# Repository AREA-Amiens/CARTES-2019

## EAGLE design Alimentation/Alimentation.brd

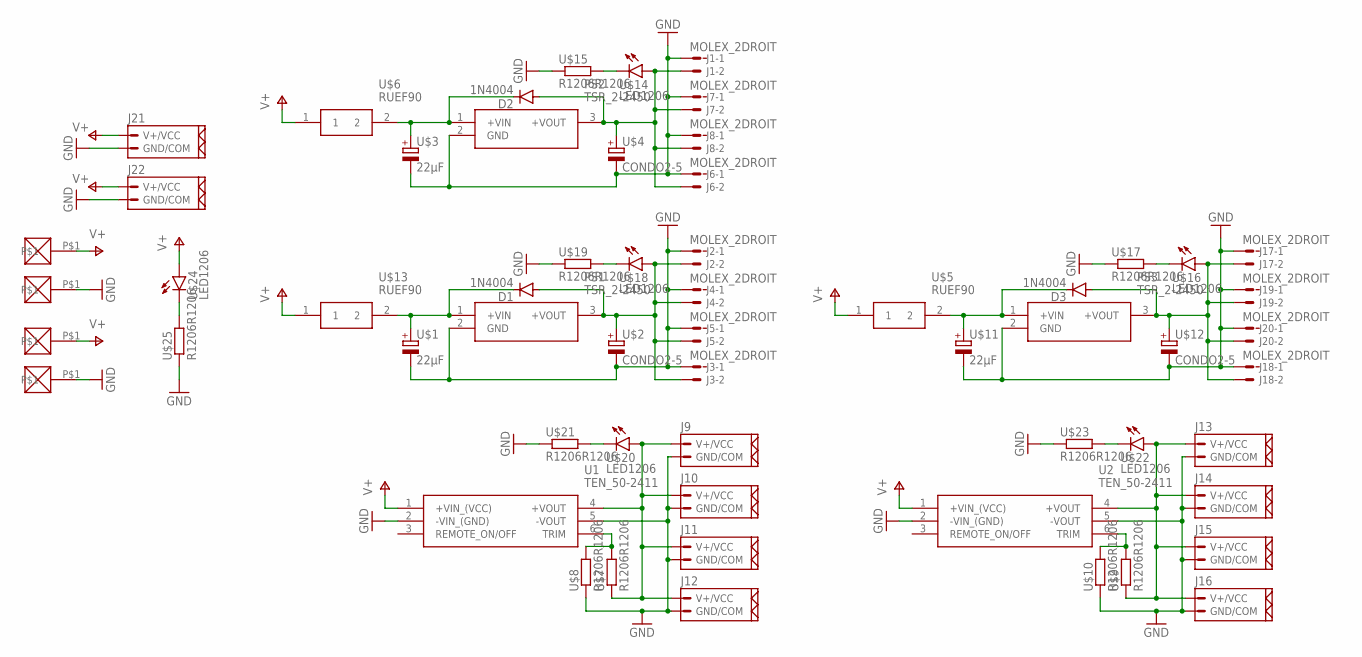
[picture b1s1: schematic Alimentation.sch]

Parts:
D1, D2, D3: 1N4004; DO41-10
J1, J2, J3, J4, J5, J6, J7, J8, J17, J18, J19, J20: MOLEX_2DROIT; CON_2_DROIT
J9, J10, J13, J14: MOLEX_2_PUISSDROIT; CON_2_PUISS_DROIT
J11, J12, J15, J16, J21, J22: MOLEX_2_PUISS90°; CON_2_PUISS_90°
PS1, PS2, PS3: TSR_2-2450; TSR-2
U1, U2: TEN_50-2411
U$1, U$3, U$11: 22µF; E2-5
U$2, U$4, U$12: CONDO2-5; E2-5
U$5, U$6, U$13: RUEF90; RUEF090
U$7, U$8, U$9, U$10, U$15, U$17, U$19, U$21, U$23, U$25: R1206R1206; R1206
U$14, U$16, U$18, U$20, U$22, U$24: LED1206; 1206
U$26, U$27, U$28, U$29: BAT_WIRE_SOLD; LARGE_PAD_BATT

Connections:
GND: J1.1, J2.1, J3.1, J4.1, J5.1, J6.1, J7.1, J8.1, J9.1 (GND/COM), J10.1 (GND/COM), J11.P$1 (GND/COM), J12.P$1 (GND/COM), J13.1 (GND/COM), J14.1 (GND/COM), J15.P$1 (GND/COM), J16.P$1 (GND/COM), J17.1, J18.1, J19.1, J20.1, J21.P$1 (GND/COM), J22.P$1 (GND/COM), PS1.2 (GND), PS2.2 (GND), PS3.2 (GND), U1.2 (-VIN_(GND)), U1.5 (-VOUT), U2.2 (-VIN_(GND)), U2.5 (-VOUT), U$1.-, U$2.-, U$3.-, U$4.-, U$8.1, U$10.1, U$11.-, U$12.-, U$15.1, U$17.1, U$19.1, U$21.1, U$23.1, U$25.1, U$26.P$1, U$28.P$1
unnamed: D1.C, PS1.1 (+VIN), U$1.+, U$13.2
unnamed: D2.C, PS2.1 (+VIN), U$3.+, U$6.2
unnamed: D2.A, J1.2, J6.2, J7.2, J8.2, PS2.3 (+VOUT), U$4.+, U$14.A
unnamed: J9.2 (V+/VCC), J10.2 (V+/VCC), J11.P$2 (V+/VCC), J12.P$2 (V+/VCC), U1.4 (+VOUT), U$7.1, U$20.A
unnamed: U1.6 (TRIM), U$7.2, U$8.2
unnamed: D1.A, J2.2, J3.2, J4.2, J5.2, PS1.3 (+VOUT), U$2.+, U$18.A
unnamed: J13.2 (V+/VCC), J14.2 (V+/VCC), J15.P$2 (V+/VCC), J16.P$2 (V+/VCC), U2.4 (+VOUT), U$9.1, U$22.A
unnamed: U2.6 (TRIM), U$9.2, U$10.2
unnamed: D3.C, PS3.1 (+VIN), U$5.2, U$11.+
unnamed: D3.A, J17.2, J18.2, J19.2, J20.2, PS3.3 (+VOUT), U$12.+, U$16.A
unnamed: U$14.C, U$15.2
unnamed: U$16.C, U$17.2
unnamed: U$18.C, U$19.2
unnamed: U$20.C, U$21.2
unnamed: U$22.C, U$23.2
unnamed: U$24.C, U$25.2
V+: J21.P$2 (V+/VCC), J22.P$2 (V+/VCC), U1.1 (+VIN_(VCC)), U2.1 (+VIN_(VCC)), U$5.1, U$6.1, U$13.1, U$24.A, U$27.P$1, U$29.P$1

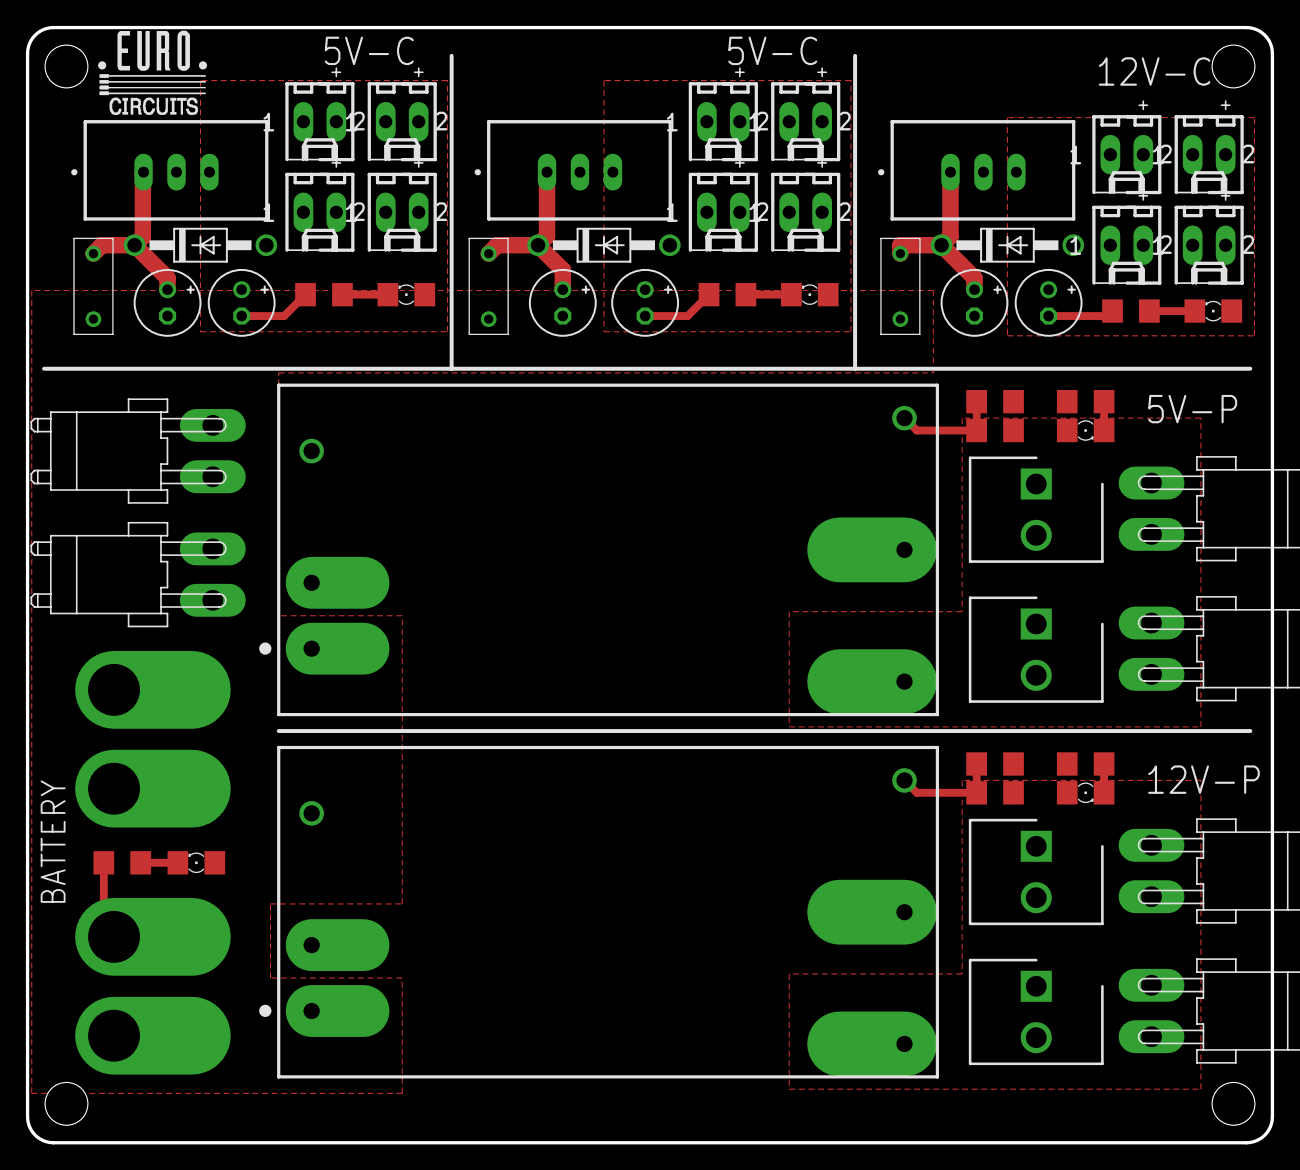
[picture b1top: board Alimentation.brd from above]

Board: 2 copper layers, 96.0 x 86.0 mm, 59 parts (0 on the bottom side), 18 nets.

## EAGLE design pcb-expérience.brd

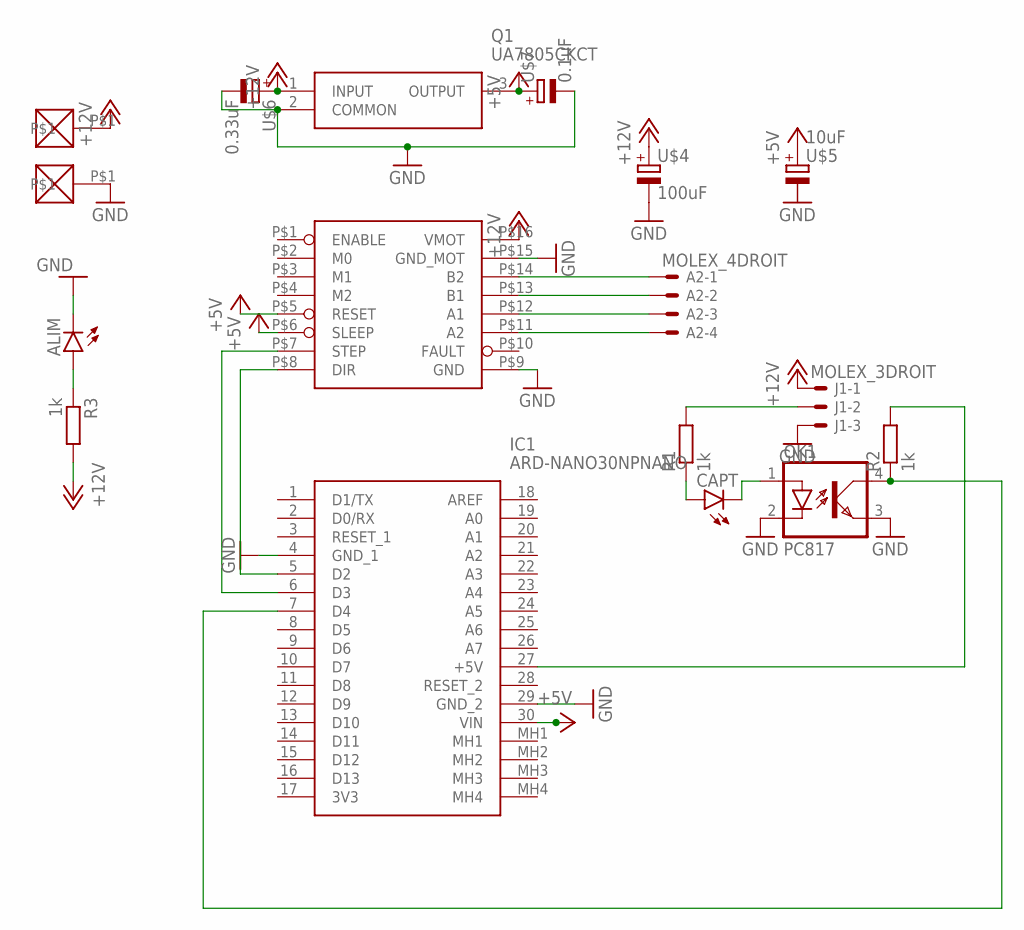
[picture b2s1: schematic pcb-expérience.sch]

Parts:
A2: MOLEX_4DROIT; CON_4_DROIT
ALIM: LED5MM
CAPT: LED5MM
IC1: ARD-NANO30NPNANO; ARDNANO30NP
J1: MOLEX_3DROIT; CON_3_DROIT
OK1: PC817; DIL04
Q1: UA7805CKCT; TO254P465X1016X1883-3P
R1, R3: 1k; 0207/2V
R2: 1k; 0207/7
U$1: DRV8825
U$2, U$3: BAT_WIRE_SOLD; LARGE_PAD_BATT
U$4: 100uF; E3,5-8
U$5: 10uF; E2-5
U$6: 0.33uF; E2-5
U$7: 0.1uF; E2-5

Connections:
+5V: IC1.30 (VIN), Q1.3 (OUTPUT), U$1.P$5 (RESET), U$1.P$6 (SLEEP), U$5.+, U$7.+
+12V: J1.1, Q1.1 (INPUT), R3.2, U$1.P$16 (VMOT), U$2.P$1, U$4.+, U$6.+
GND: ALIM.K (C), IC1.4 (GND_1), IC1.29 (GND_2), J1.3, OK1.2 (C), OK1.3 (EMIT), Q1.2 (COMMON), U$1.P$9 (GND), U$1.P$15 (GND_MOT), U$3.P$1, U$4.-, U$6.-, U$7.-
unnamed: J1.2, R1.2
unnamed: IC1.7 (D4), OK1.4 (COL), R2.1
unnamed: IC1.27 (+5V), R2.2
unnamed: A2.4, U$1.P$11 (A2)
unnamed: A2.3, U$1.P$12 (A1)
unnamed: A2.2, U$1.P$13 (B1)
unnamed: A2.1, U$1.P$14 (B2)
unnamed: ALIM.A, R3.1
unnamed: CAPT.K (C), OK1.1 (A)
unnamed: CAPT.A, R1.1
unnamed: IC1.5 (D2), U$1.P$8 (DIR)
unnamed: IC1.6 (D3), U$1.P$7 (STEP)

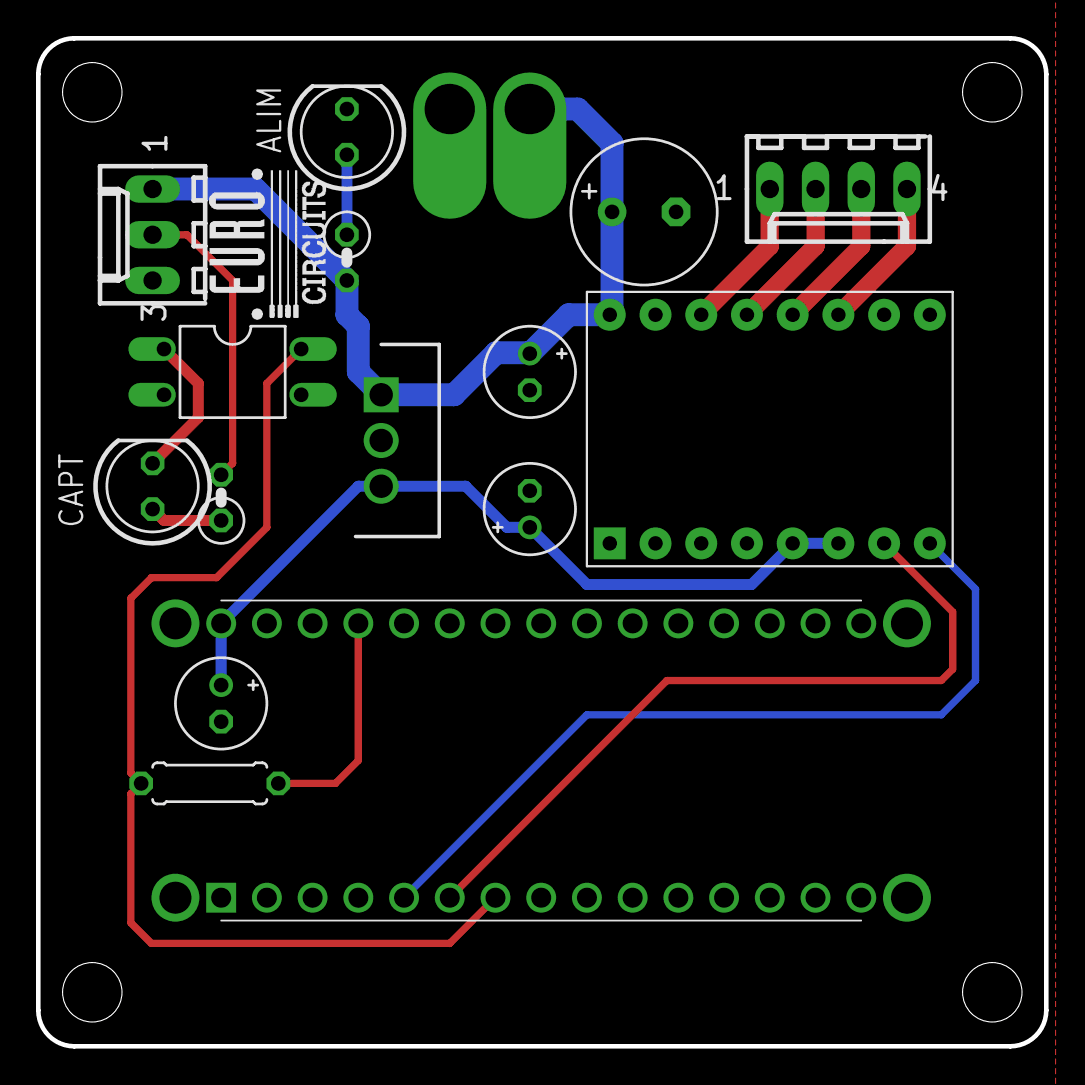
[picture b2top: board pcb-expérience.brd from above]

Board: 2 copper layers, 56.0 x 56.0 mm, 17 parts (0 on the bottom side), 15 nets.

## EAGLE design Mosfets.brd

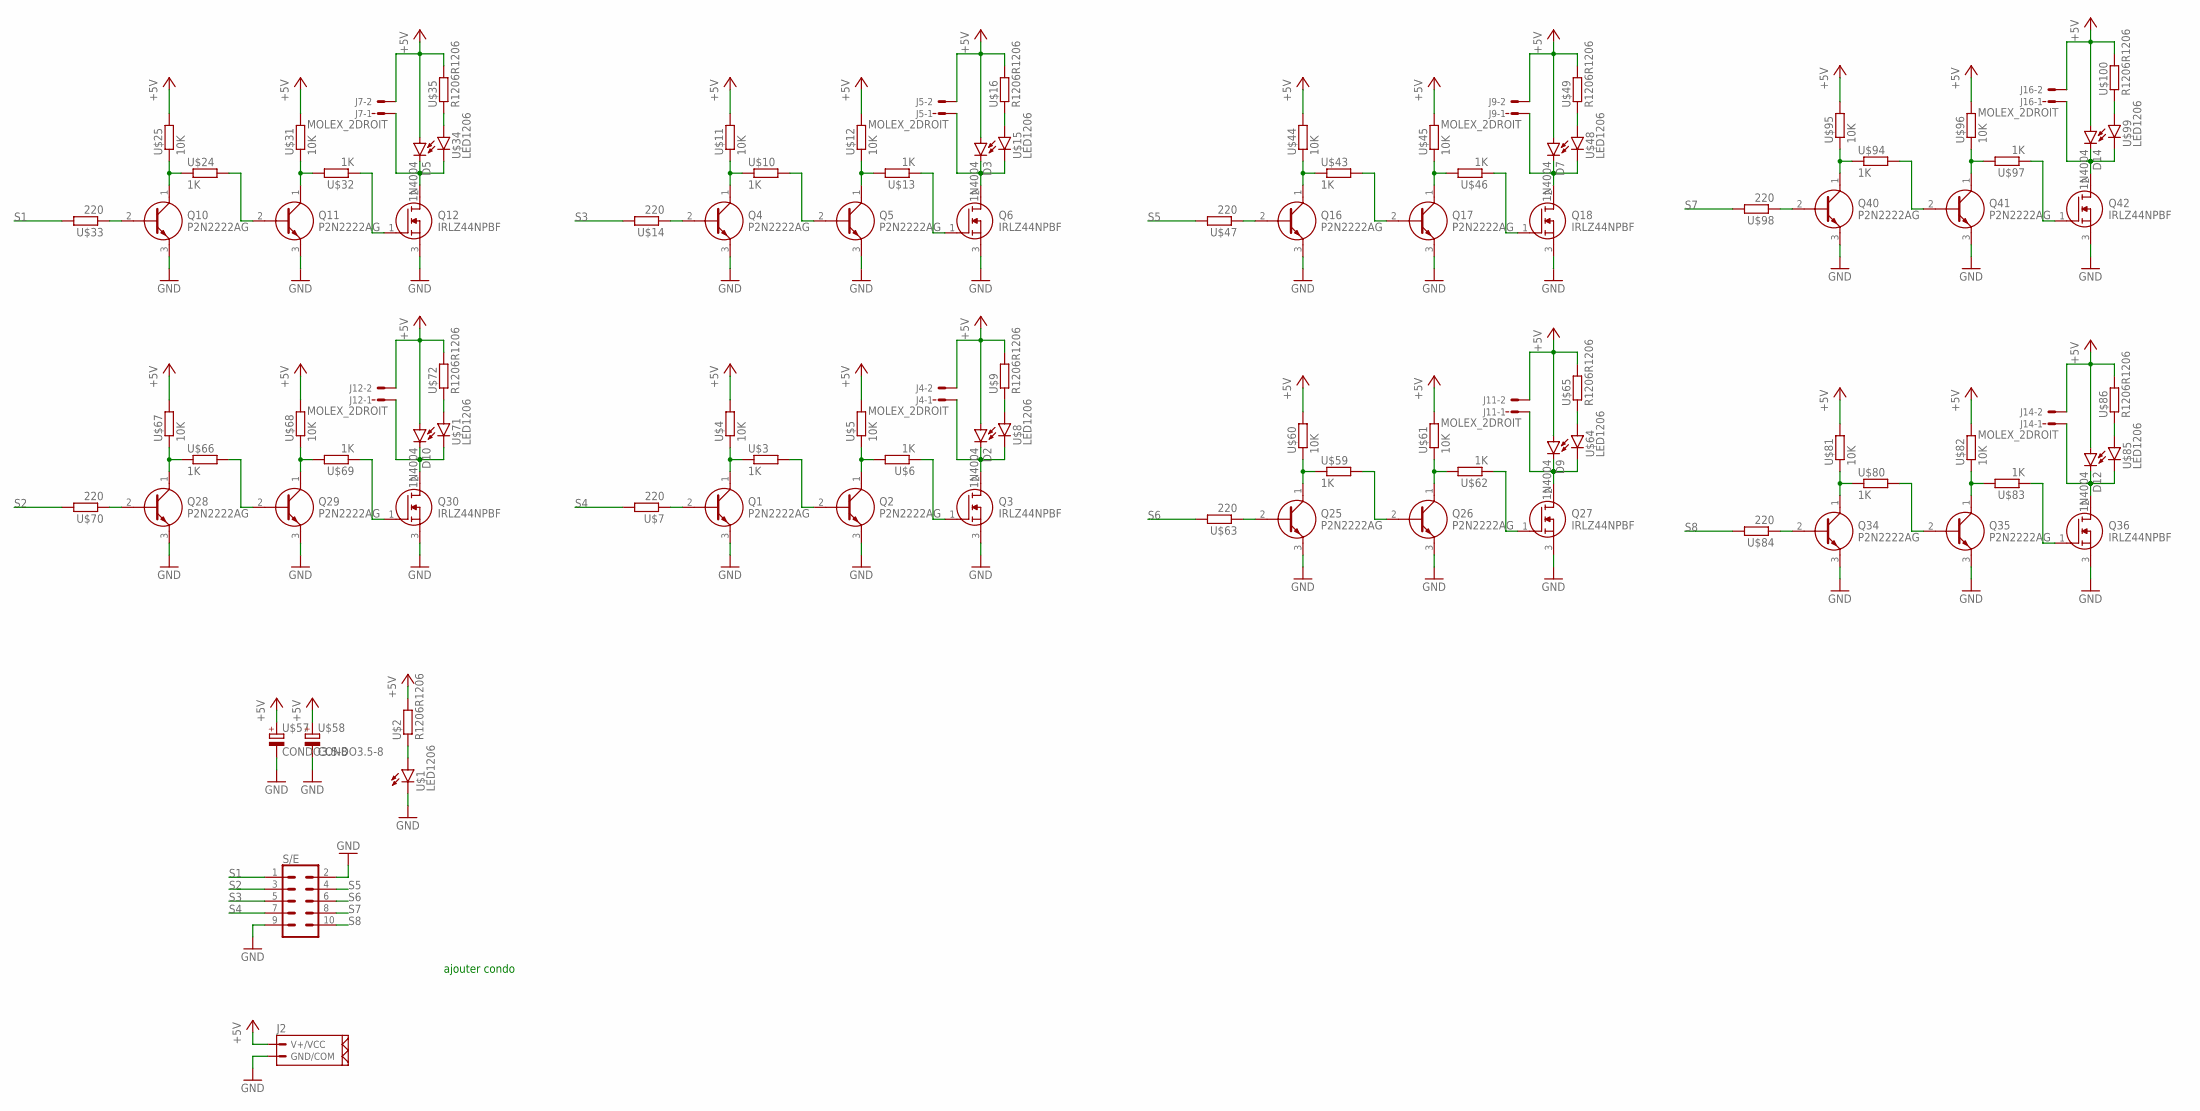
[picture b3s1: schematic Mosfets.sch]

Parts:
D2, D3, D5, D7, D9, D10, D12, D14: 1N4004; DO41-10
J2: MOLEX_2_PUISS90°; CON_2_PUISS_90°
J4, J5, J7, J9, J11, J12, J14, J16: MOLEX_2DROIT; CON_2_DROIT
Q1, Q2, Q4, Q5, Q10, Q11, Q16, Q17, Q25, Q26, Q28, Q29, Q34, Q35, Q40, Q41: P2N2222AG; TO-92
Q3, Q6, Q12, Q18, Q27, Q30, Q36, Q42: IRLZ44NPBF; TO254P469X1042X1967-3P
S/E: CON_5X2SHD; 2X5-SHROUDED
U$1, U$8, U$15, U$34, U$48, U$64, U$71, U$85, U$99: LED1206; 1206
U$2, U$9, U$16, U$35, U$49, U$65, U$72, U$86, U$100: R1206R1206; R1206
U$3, U$6, U$10, U$13, U$24, U$32, U$43, U$46, U$59, U$62, U$66, U$69, U$80, U$83, U$94, U$97: 1K; R1206
U$4, U$5, U$11, U$12, U$25, U$31, U$44, U$45, U$60, U$61, U$67, U$68, U$81, U$82, U$95, U$96: 10K; R1206
U$7, U$14, U$33, U$47, U$63, U$70, U$84, U$98: 220; R1206
U$57, U$58: CONDO3.5-8; E3,5-8

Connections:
+5V: D2.A, D3.A, D5.A, D7.A, D9.A, D10.A, D12.A, D14.A, J2.P$2 (V+/VCC), J4.2, J5.2, J7.2, J9.2, J11.2, J12.2, J14.2, J16.2, U$2.2, U$4.2, U$5.2, U$9.2, U$11.2, U$12.2, U$16.2, U$25.2, U$31.2, U$35.2, U$44.2, U$45.2, U$49.2, U$57.+, U$58.+, U$60.2, U$61.2, U$65.2, U$67.2, U$68.2, U$72.2, U$81.2, U$82.2, U$86.2, U$95.2, U$96.2, U$100.2
GND: J2.P$1 (GND/COM), Q1.3 (E), Q2.3 (E), Q3.3 (S), Q4.3 (E), Q5.3 (E), Q6.3 (S), Q10.3 (E), Q11.3 (E), Q12.3 (S), Q16.3 (E), Q17.3 (E), Q18.3 (S), Q25.3 (E), Q26.3 (E), Q27.3 (S), Q28.3 (E), Q29.3 (E), Q30.3 (S), Q34.3 (E), Q35.3 (E), Q36.3 (S), Q40.3 (E), Q41.3 (E), Q42.3 (S), S/E.2, S/E.9, U$1.C, U$57.-, U$58.-
unnamed: Q1.1 (C), U$3.1, U$4.1
unnamed: Q2.1 (C), U$5.1, U$6.2
unnamed: Q1.2 (B), U$7.1
unnamed: Q2.2 (B), U$3.2
unnamed: Q3.1 (G), U$6.1
unnamed: D2.C, J4.1, Q3.2 (D), U$8.C
unnamed: U$8.A, U$9.1
unnamed: Q4.1 (C), U$10.1, U$11.1
unnamed: Q5.1 (C), U$12.1, U$13.2
unnamed: Q4.2 (B), U$14.1
unnamed: Q5.2 (B), U$10.2
unnamed: Q6.1 (G), U$13.1
unnamed: D3.C, J5.1, Q6.2 (D), U$15.C
unnamed: Q28.1 (C), U$66.1, U$67.1
unnamed: U$15.A, U$16.1
unnamed: U$1.A, U$2.1
unnamed: Q10.1 (C), U$24.1, U$25.1
unnamed: Q11.1 (C), U$31.1, U$32.2
unnamed: Q10.2 (B), U$33.1
unnamed: Q11.2 (B), U$24.2
unnamed: Q12.1 (G), U$32.1
unnamed: D5.C, J7.1, Q12.2 (D), U$34.C
unnamed: U$34.A, U$35.1
unnamed: Q16.1 (C), U$43.1, U$44.1
unnamed: Q17.1 (C), U$45.1, U$46.2
unnamed: Q16.2 (B), U$47.1
unnamed: Q17.2 (B), U$43.2
unnamed: Q18.1 (G), U$46.1
unnamed: D7.C, J9.1, Q18.2 (D), U$48.C
unnamed: U$48.A, U$49.1
unnamed: Q29.1 (C), U$68.1, U$69.2
unnamed: Q25.1 (C), U$59.1, U$60.1
unnamed: Q26.1 (C), U$61.1, U$62.2
unnamed: Q25.2 (B), U$63.1
unnamed: Q26.2 (B), U$59.2
unnamed: Q27.1 (G), U$62.1
unnamed: D9.C, J11.1, Q27.2 (D), U$64.C
unnamed: U$64.A, U$65.1
unnamed: Q28.2 (B), U$70.1
unnamed: Q29.2 (B), U$66.2
unnamed: Q30.1 (G), U$69.1
unnamed: D10.C, J12.1, Q30.2 (D), U$71.C
unnamed: U$71.A, U$72.1
unnamed: Q34.1 (C), U$80.1, U$81.1
unnamed: Q35.1 (C), U$82.1, U$83.2
unnamed: Q34.2 (B), U$84.1
unnamed: Q35.2 (B), U$80.2
unnamed: Q36.1 (G), U$83.1
unnamed: D12.C, J14.1, Q36.2 (D), U$85.C
unnamed: U$85.A, U$86.1
unnamed: Q40.1 (C), U$94.1, U$95.1
unnamed: Q41.1 (C), U$96.1, U$97.2
unnamed: Q40.2 (B), U$98.1
unnamed: Q41.2 (B), U$94.2
unnamed: Q42.1 (G), U$97.1
unnamed: D14.C, J16.1, Q42.2 (D), U$99.C
unnamed: U$99.A, U$100.1
S1: S/E.1, U$33.2
S2: S/E.3, U$70.2
S3: S/E.5, U$14.2
S4: S/E.7, U$7.2
S5: S/E.4, U$47.2
S6: S/E.6, U$63.2
S7: S/E.8, U$98.2
S8: S/E.10, U$84.2

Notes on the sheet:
ajouter condo

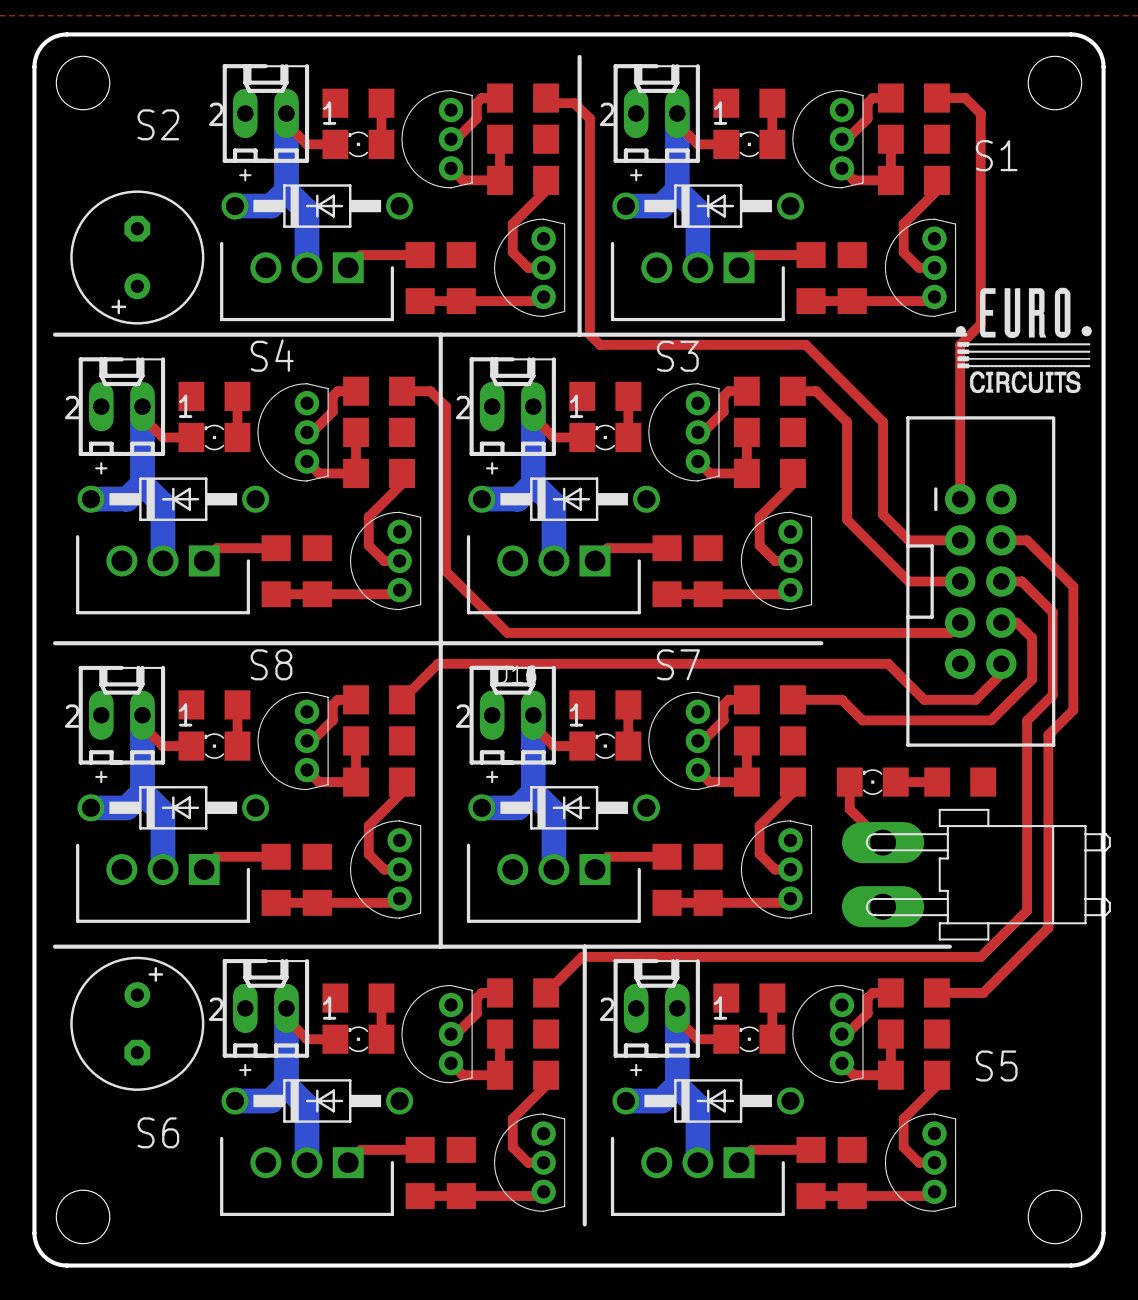
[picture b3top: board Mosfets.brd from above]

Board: 2 copper layers, 66.0 x 76.0 mm, 102 parts (0 on the bottom side), 67 nets.

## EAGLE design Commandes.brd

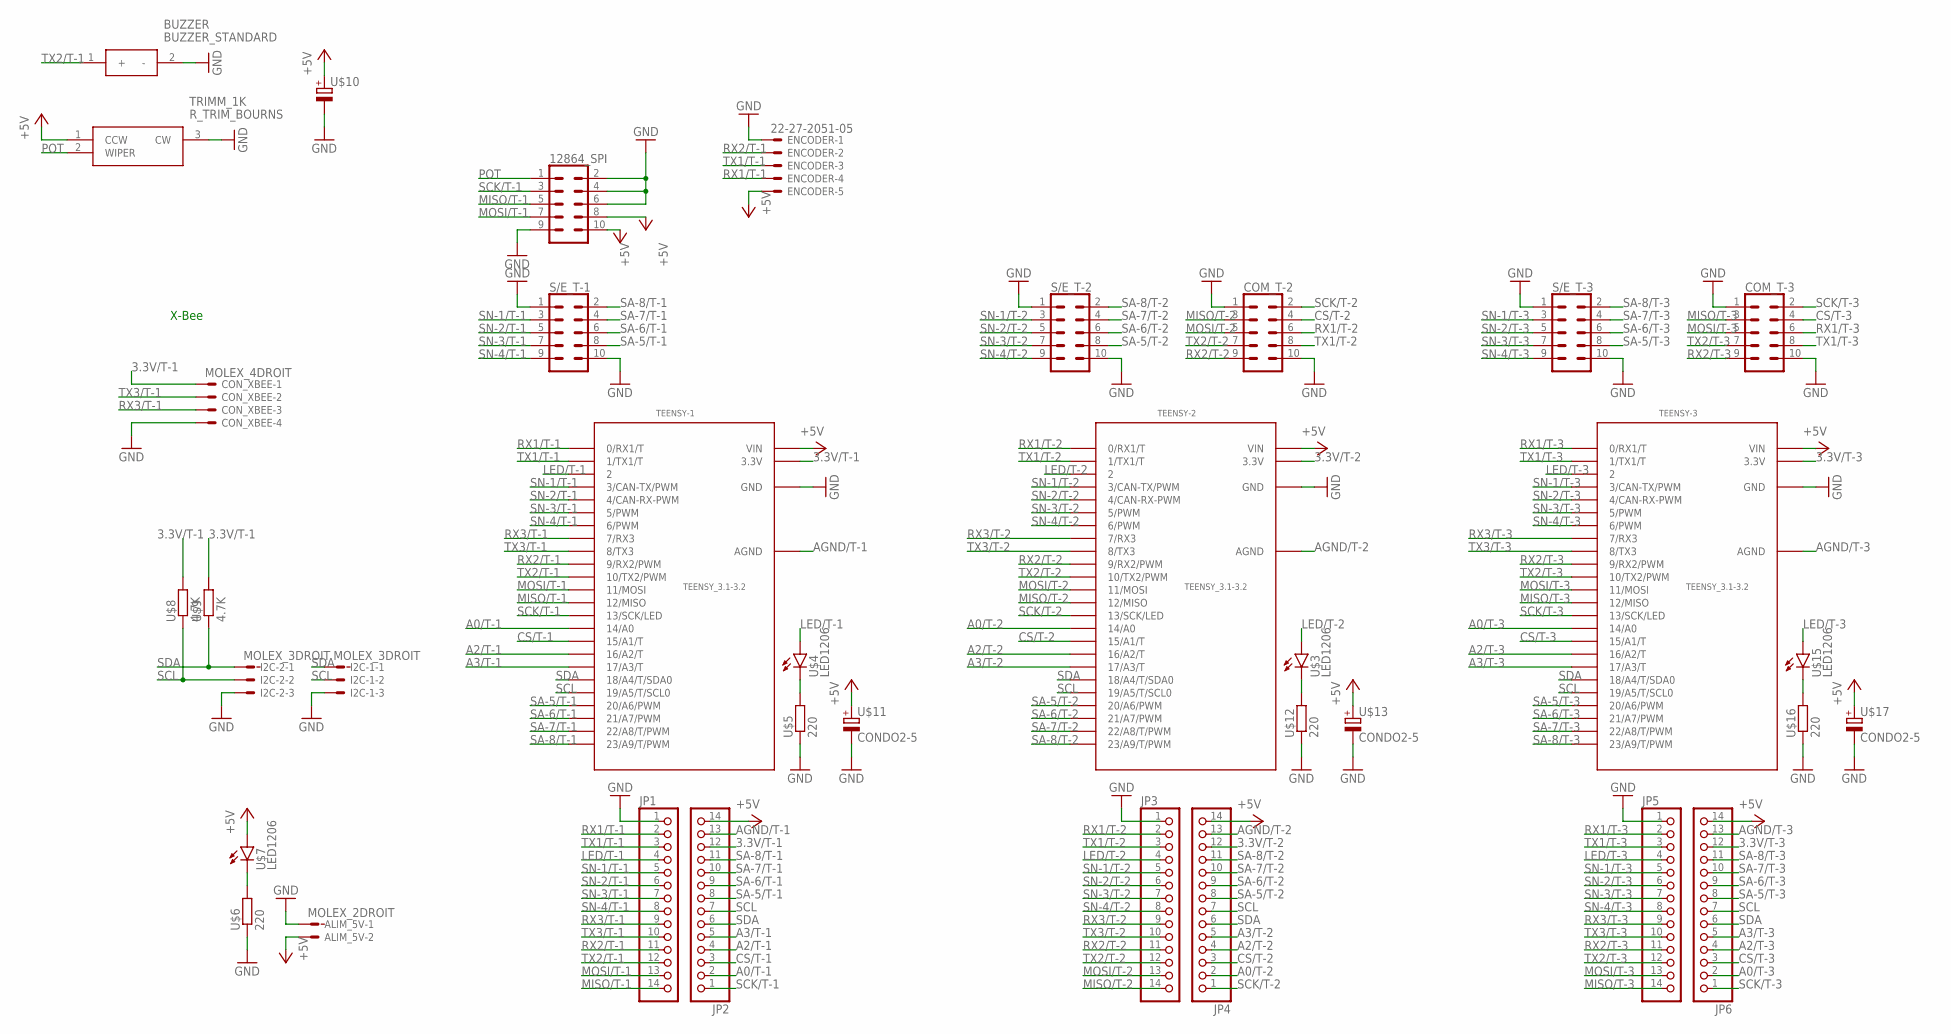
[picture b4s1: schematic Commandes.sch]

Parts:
12864_SPI: CON_5X2SHD; 2X5-SHROUDED
ALIM_5V: MOLEX_2DROIT; CON_2_DROIT
BUZZER: BUZZER_STANDARD; CEM-1203(42)
COM_T-2, COM_T-3: CON_5X2SHD; 2X5-SHROUDED
CON_XBEE: MOLEX_4DROIT; CON_4_DROIT
ENCODER: 22-27-2051-05; 6410-05
I2C-1, I2C-2: MOLEX_3DROIT; CON_3_DROIT
JP1, JP2, JP3, JP4, JP5, JP6: PINHD-1X14_2.54; 1X14
S/E_T-1, S/E_T-2, S/E_T-3: CON_5X2SHD; 2X5-SHROUDED
TEENSY-1, TEENSY-2, TEENSY-3: TEENSY_3.1-3.2; TEENSY_3.0-3.2&LC_OUTER_ROW
TRIMM_1K: R_TRIM_BOURNS; 3362P_1
U$3, U$4, U$7, U$15: LED1206; 1206
U$5, U$6, U$12, U$16: 220; R1206
U$8, U$9: 4.7K; R1206
U$10, U$11, U$13, U$17: CONDO2-5; E2-5

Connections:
3.3V/T-1: CON_XBEE.1, JP2.12, TEENSY-1.3.3V, U$8.2, U$9.2
3.3V/T-2: JP4.12, TEENSY-2.3.3V
3.3V/T-3: JP6.12, TEENSY-3.3.3V
+5V: 12864_SPI.8, 12864_SPI.10, ALIM_5V.2, ENCODER.5, JP2.14, JP4.14, JP6.14, TEENSY-1.V_IN (VIN), TEENSY-2.V_IN (VIN), TEENSY-3.V_IN (VIN), TRIMM_1K.1 (CCW), U$7.A, U$10.+, U$11.+, U$13.+, U$17.+
A0/T-1: JP2.2, TEENSY-1.14/A0
A0/T-2: JP4.2, TEENSY-2.14/A0
A0/T-3: JP6.2, TEENSY-3.14/A0
A2/T-1: JP2.4, TEENSY-1.16/A2 (16/A2/T)
A2/T-2: JP4.4, TEENSY-2.16/A2 (16/A2/T)
A2/T-3: JP6.4, TEENSY-3.16/A2 (16/A2/T)
A3/T-1: JP2.5, TEENSY-1.17/A3 (17/A3/T)
A3/T-2: JP4.5, TEENSY-2.17/A3 (17/A3/T)
A3/T-3: JP6.5, TEENSY-3.17/A3 (17/A3/T)
AGND/T-1: JP2.13, TEENSY-1.AGND
AGND/T-2: JP4.13, TEENSY-2.AGND
AGND/T-3: JP6.13, TEENSY-3.AGND
CS/T-1: JP2.3, TEENSY-1.15/A1 (15/A1/T)
CS/T-2: COM_T-2.4, JP4.3, TEENSY-2.15/A1 (15/A1/T)
CS/T-3: COM_T-3.4, JP6.3, TEENSY-3.15/A1 (15/A1/T)
GND: 12864_SPI.2, 12864_SPI.4, 12864_SPI.6, 12864_SPI.9, ALIM_5V.1, BUZZER.2 (-), COM_T-2.1, COM_T-2.10, COM_T-3.1, COM_T-3.10, CON_XBEE.4, ENCODER.1, I2C-1.3, I2C-2.3, JP1.1, JP3.1, JP5.1, S/E_T-1.1, S/E_T-1.10, S/E_T-2.1, S/E_T-2.10, S/E_T-3.1, S/E_T-3.10, TEENSY-1.GND, TEENSY-2.GND, TEENSY-3.GND, TRIMM_1K.3 (CW), U$5.1, U$6.1, U$10.-, U$11.-, U$12.1, U$13.-, U$16.1, U$17.-
LED/T-1: JP1.4, TEENSY-1.2, U$4.A
LED/T-2: JP3.4, TEENSY-2.2, U$3.A
LED/T-3: JP5.4, TEENSY-3.2, U$15.A
MISO/T-1: 12864_SPI.5, JP1.14, TEENSY-1.12 (12/MISO)
MISO/T-2: COM_T-2.3, JP3.14, TEENSY-2.12 (12/MISO)
MISO/T-3: COM_T-3.3, JP5.14, TEENSY-3.12 (12/MISO)
MOSI/T-1: 12864_SPI.7, JP1.13, TEENSY-1.11 (11/MOSI)
MOSI/T-2: COM_T-2.5, JP3.13, TEENSY-2.11 (11/MOSI)
MOSI/T-3: COM_T-3.5, JP5.13, TEENSY-3.11 (11/MOSI)
unnamed: U$4.C, U$5.2
unnamed: U$3.C, U$12.2
unnamed: U$15.C, U$16.2
unnamed: U$6.2, U$7.C
POT: 12864_SPI.1, TRIMM_1K.2 (WIPER)
RX1/T-1: ENCODER.4, JP1.2, TEENSY-1.0 (0/RX1/T)
RX1/T-2: COM_T-2.6, JP3.2, TEENSY-2.0 (0/RX1/T)
RX1/T-3: COM_T-3.6, JP5.2, TEENSY-3.0 (0/RX1/T)
RX2/T-1: ENCODER.2, JP1.11, TEENSY-1.9 (9/RX2/PWM)
RX2/T-2: COM_T-2.9, JP3.11, TEENSY-2.9 (9/RX2/PWM)
RX2/T-3: COM_T-3.9, JP5.11, TEENSY-3.9 (9/RX2/PWM)
RX3/T-1: CON_XBEE.3, JP1.9, TEENSY-1.7 (7/RX3)
RX3/T-2: JP3.9, TEENSY-2.7 (7/RX3)
RX3/T-3: JP5.9, TEENSY-3.7 (7/RX3)
SA-5/T-1: JP2.8, S/E_T-1.8, TEENSY-1.20/A6 (20/A6/PWM)
SA-5/T-2: JP4.8, S/E_T-2.8, TEENSY-2.20/A6 (20/A6/PWM)
SA-5/T-3: JP6.8, S/E_T-3.8, TEENSY-3.20/A6 (20/A6/PWM)
SA-6/T-1: JP2.9, S/E_T-1.6, TEENSY-1.21/A7 (21/A7/PWM)
SA-6/T-2: JP4.9, S/E_T-2.6, TEENSY-2.21/A7 (21/A7/PWM)
SA-6/T-3: JP6.9, S/E_T-3.6, TEENSY-3.21/A7 (21/A7/PWM)
SA-7/T-1: JP2.10, S/E_T-1.4, TEENSY-1.22/A8 (22/A8/T/PWM)
SA-7/T-2: JP4.10, S/E_T-2.4, TEENSY-2.22/A8 (22/A8/T/PWM)
SA-7/T-3: JP6.10, S/E_T-3.4, TEENSY-3.22/A8 (22/A8/T/PWM)
SA-8/T-1: JP2.11, S/E_T-1.2, TEENSY-1.23/A9 (23/A9/T/PWM)
SA-8/T-2: JP4.11, S/E_T-2.2, TEENSY-2.23/A9 (23/A9/T/PWM)
SA-8/T-3: JP6.11, S/E_T-3.2, TEENSY-3.23/A9 (23/A9/T/PWM)
SCK/T-1: 12864_SPI.3, JP2.1, TEENSY-1.13 (13/SCK/LED)
SCK/T-2: COM_T-2.2, JP4.1, TEENSY-2.13 (13/SCK/LED)
SCK/T-3: COM_T-3.2, JP6.1, TEENSY-3.13 (13/SCK/LED)
SCL: I2C-1.2, I2C-2.2, JP2.7, JP4.7, JP6.7, TEENSY-1.19/A5 (19/A5/T/SCL0), TEENSY-2.19/A5 (19/A5/T/SCL0), TEENSY-3.19/A5 (19/A5/T/SCL0), U$8.1
SDA: I2C-1.1, I2C-2.1, JP2.6, JP4.6, JP6.6, TEENSY-1.18/A4 (18/A4/T/SDA0), TEENSY-2.18/A4 (18/A4/T/SDA0), TEENSY-3.18/A4 (18/A4/T/SDA0), U$9.1
SN-1/T-1: JP1.5, S/E_T-1.3, TEENSY-1.3 (3/CAN-TX/PWM)
SN-1/T-2: JP3.5, S/E_T-2.3, TEENSY-2.3 (3/CAN-TX/PWM)
SN-1/T-3: JP5.5, S/E_T-3.3, TEENSY-3.3 (3/CAN-TX/PWM)
SN-2/T-1: JP1.6, S/E_T-1.5, TEENSY-1.4 (4/CAN-RX-PWM)
SN-2/T-2: JP3.6, S/E_T-2.5, TEENSY-2.4 (4/CAN-RX-PWM)
SN-2/T-3: JP5.6, S/E_T-3.5, TEENSY-3.4 (4/CAN-RX-PWM)
SN-3/T-1: JP1.7, S/E_T-1.7, TEENSY-1.5 (5/PWM)
SN-3/T-2: JP3.7, S/E_T-2.7, TEENSY-2.5 (5/PWM)
SN-3/T-3: JP5.7, S/E_T-3.7, TEENSY-3.5 (5/PWM)
SN-4/T-1: JP1.8, S/E_T-1.9, TEENSY-1.6 (6/PWM)
SN-4/T-2: JP3.8, S/E_T-2.9, TEENSY-2.6 (6/PWM)
SN-4/T-3: JP5.8, S/E_T-3.9, TEENSY-3.6 (6/PWM)
TX1/T-1: ENCODER.3, JP1.3, TEENSY-1.1 (1/TX1/T)
TX1/T-2: COM_T-2.8, JP3.3, TEENSY-2.1 (1/TX1/T)
TX1/T-3: COM_T-3.8, JP5.3, TEENSY-3.1 (1/TX1/T)
TX2/T-1: BUZZER.1 (+), JP1.12, TEENSY-1.10 (10/TX2/PWM)
TX2/T-2: COM_T-2.7, JP3.12, TEENSY-2.10 (10/TX2/PWM)
TX2/T-3: COM_T-3.7, JP5.12, TEENSY-3.10 (10/TX2/PWM)
TX3/T-1: CON_XBEE.2, JP1.10, TEENSY-1.8 (8/TX3)
TX3/T-2: JP3.10, TEENSY-2.8 (8/TX3)
TX3/T-3: JP5.10, TEENSY-3.8 (8/TX3)

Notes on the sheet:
X-Bee

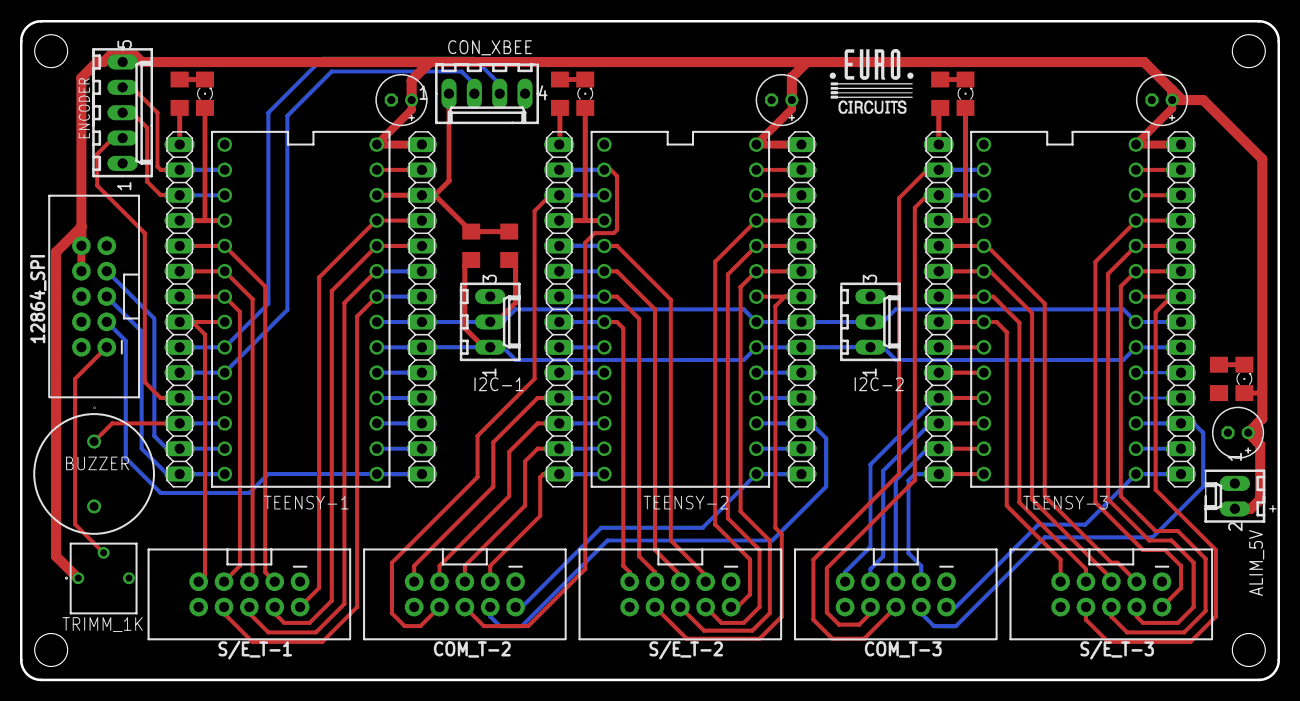
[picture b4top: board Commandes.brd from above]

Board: 2 copper layers, 126.0 x 66.0 mm, 36 parts (0 on the bottom side), 81 nets.

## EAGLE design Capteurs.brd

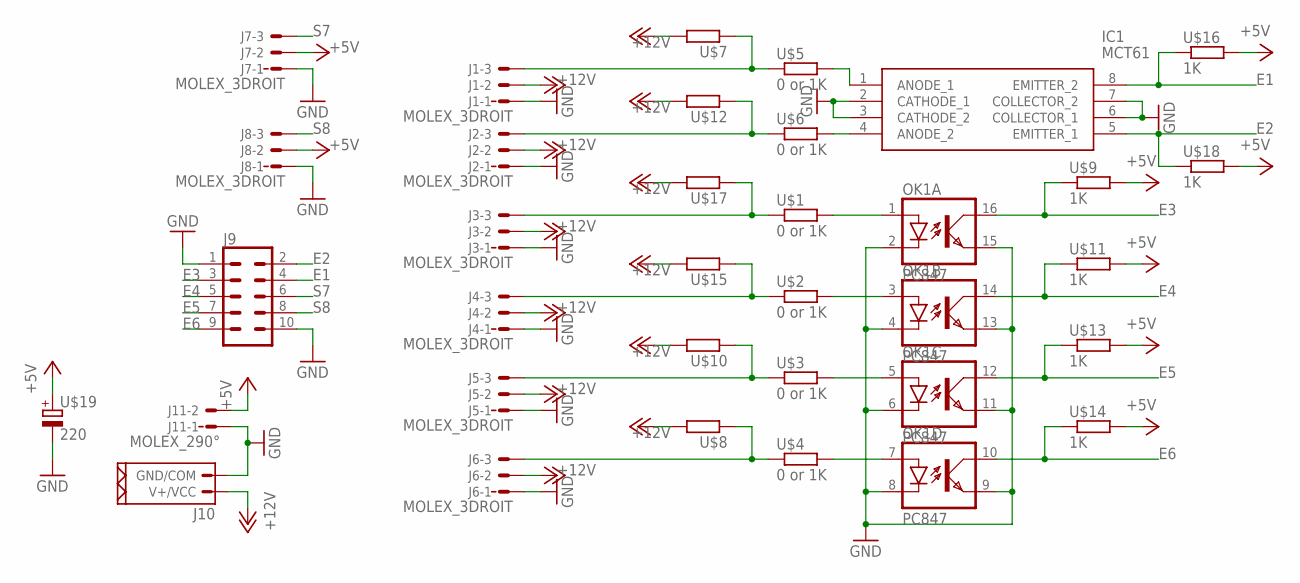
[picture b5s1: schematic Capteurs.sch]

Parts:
IC1: MCT61; DIP762W56P254L940H508Q8N
J1, J2, J3, J4, J5, J6, J7, J8: MOLEX_3DROIT; CON_3_DROIT
J9: CON_5X2SHD; 2X5-SHROUDED
J10: MOLEX_2_PUISS90°; CON_2_PUISS_90°
J11: MOLEX_290°; CON_2_90°
OK1: PC847; DIL16
U$1, U$2, U$3, U$4, U$5, U$6: 0 or 1K; R1206
U$7, U$8, U$10, U$12, U$15, U$17: NULL or 500; R1206
U$9, U$11, U$13, U$14, U$16, U$18: 1K; R1206
U$19: 220; E3,5-8

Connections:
+5V: J7.2, J8.2, J11.2, U$9.2, U$11.2, U$13.2, U$14.2, U$16.2, U$18.2, U$19.+
+12V: J1.2, J2.2, J3.2, J4.2, J5.2, J6.2, J10.P$2 (V+/VCC), U$7.2, U$8.2, U$10.2, U$12.2, U$15.2, U$17.2
E1: IC1.8 (EMITTER_2), J9.4, U$16.1
E2: IC1.5 (EMITTER_1), J9.2, U$18.1
E3: J9.3, OK1.16 (COL), U$9.1
E4: J9.5, OK1.14 (COL), U$11.1
E5: J9.7, OK1.12 (COL), U$13.1
E6: J9.9, OK1.10 (COL), U$14.1
GND: IC1.2 (CATHODE_1), IC1.3 (CATHODE_2), IC1.6 (COLLECTOR_1), IC1.7 (COLLECTOR_2), J1.1, J2.1, J3.1, J4.1, J5.1, J6.1, J7.1, J8.1, J9.1, J9.10, J10.P$1 (GND/COM), J11.1, OK1.2 (C), OK1.4 (C), OK1.6 (C), OK1.8 (C), OK1.9 (EMIT), OK1.11 (EMIT), OK1.13 (EMIT), OK1.15 (EMIT), U$19.-
unnamed: OK1.1 (A), U$1.2
unnamed: OK1.3 (A), U$2.2
unnamed: OK1.5 (A), U$3.2
unnamed: OK1.7 (A), U$4.2
unnamed: J3.3, U$1.1, U$17.1
unnamed: J4.3, U$2.1, U$15.1
unnamed: IC1.1 (ANODE_1), U$5.2
unnamed: IC1.4 (ANODE_2), U$6.2
unnamed: J5.3, U$3.1, U$10.1
unnamed: J6.3, U$4.1, U$8.1
unnamed: J2.3, U$6.1, U$12.1
unnamed: J1.3, U$5.1, U$7.1
S7: J7.3, J9.6
S8: J8.3, J9.8

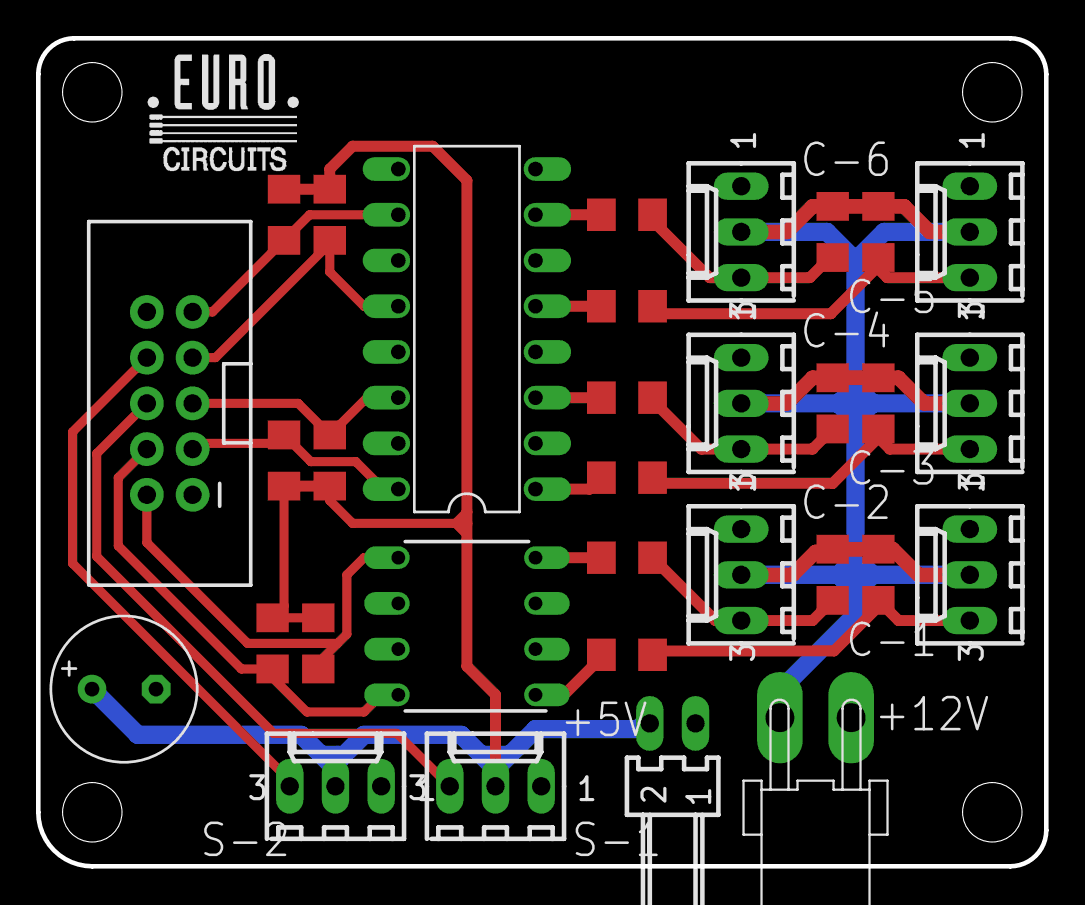
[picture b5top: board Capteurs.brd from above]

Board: 2 copper layers, 56.0 x 46.0 mm, 32 parts (0 on the bottom side), 23 nets.

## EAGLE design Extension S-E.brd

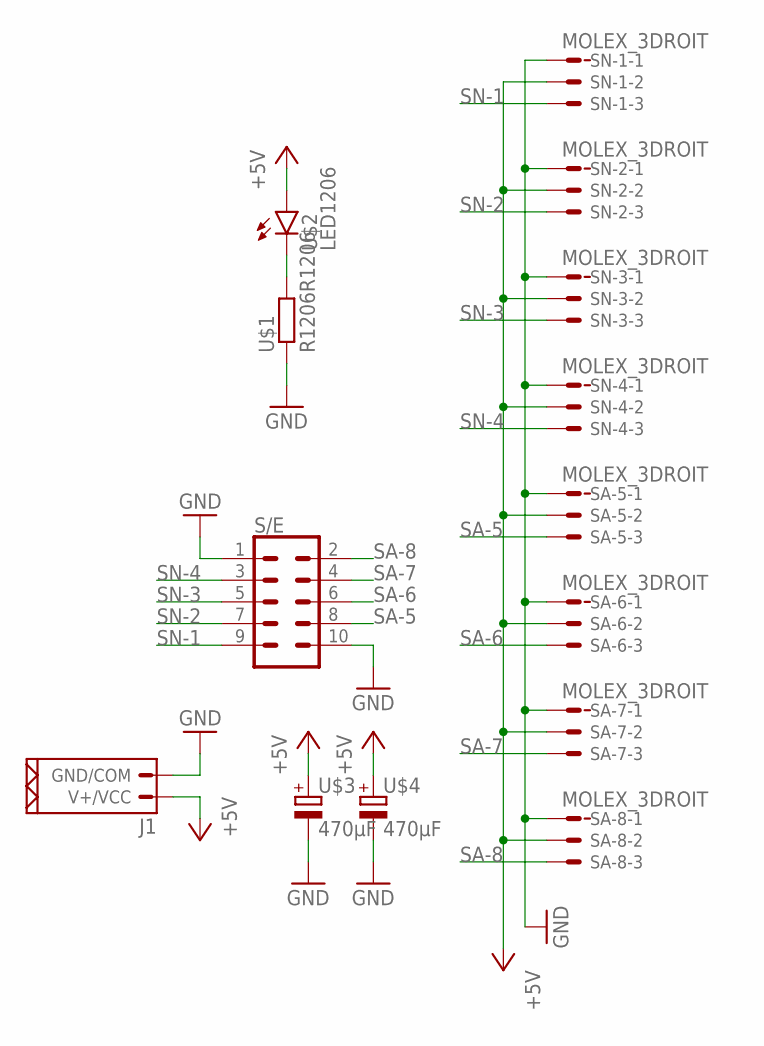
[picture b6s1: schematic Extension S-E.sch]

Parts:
J1: MOLEX_2_PUISS90°; CON_2_PUISS_90°
S/E: CON_5X2SHD; 2X5-SHROUDED
SA-5, SA-6, SA-7, SA-8: MOLEX_3DROIT; CON_3_DROIT
SN-1, SN-2, SN-3, SN-4: MOLEX_3DROIT; CON_3_DROIT
U$1: R1206R1206; R1206
U$2: LED1206; 1206
U$3, U$4: 470µF; E3,5-8

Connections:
+5V: J1.P$2 (V+/VCC), SA-5.2, SA-6.2, SA-7.2, SA-8.2, SN-1.2, SN-2.2, SN-3.2, SN-4.2, U$2.A, U$3.+, U$4.+
GND: J1.P$1 (GND/COM), S/E.1, S/E.10, SA-5.1, SA-6.1, SA-7.1, SA-8.1, SN-1.1, SN-2.1, SN-3.1, SN-4.1, U$1.1, U$3.-, U$4.-
unnamed: U$1.2, U$2.C
SA-5: S/E.8, SA-5.3
SA-6: S/E.6, SA-6.3
SA-7: S/E.4, SA-7.3
SA-8: S/E.2, SA-8.3
SN-1: S/E.9, SN-1.3
SN-2: S/E.7, SN-2.3
SN-3: S/E.5, SN-3.3
SN-4: S/E.3, SN-4.3
